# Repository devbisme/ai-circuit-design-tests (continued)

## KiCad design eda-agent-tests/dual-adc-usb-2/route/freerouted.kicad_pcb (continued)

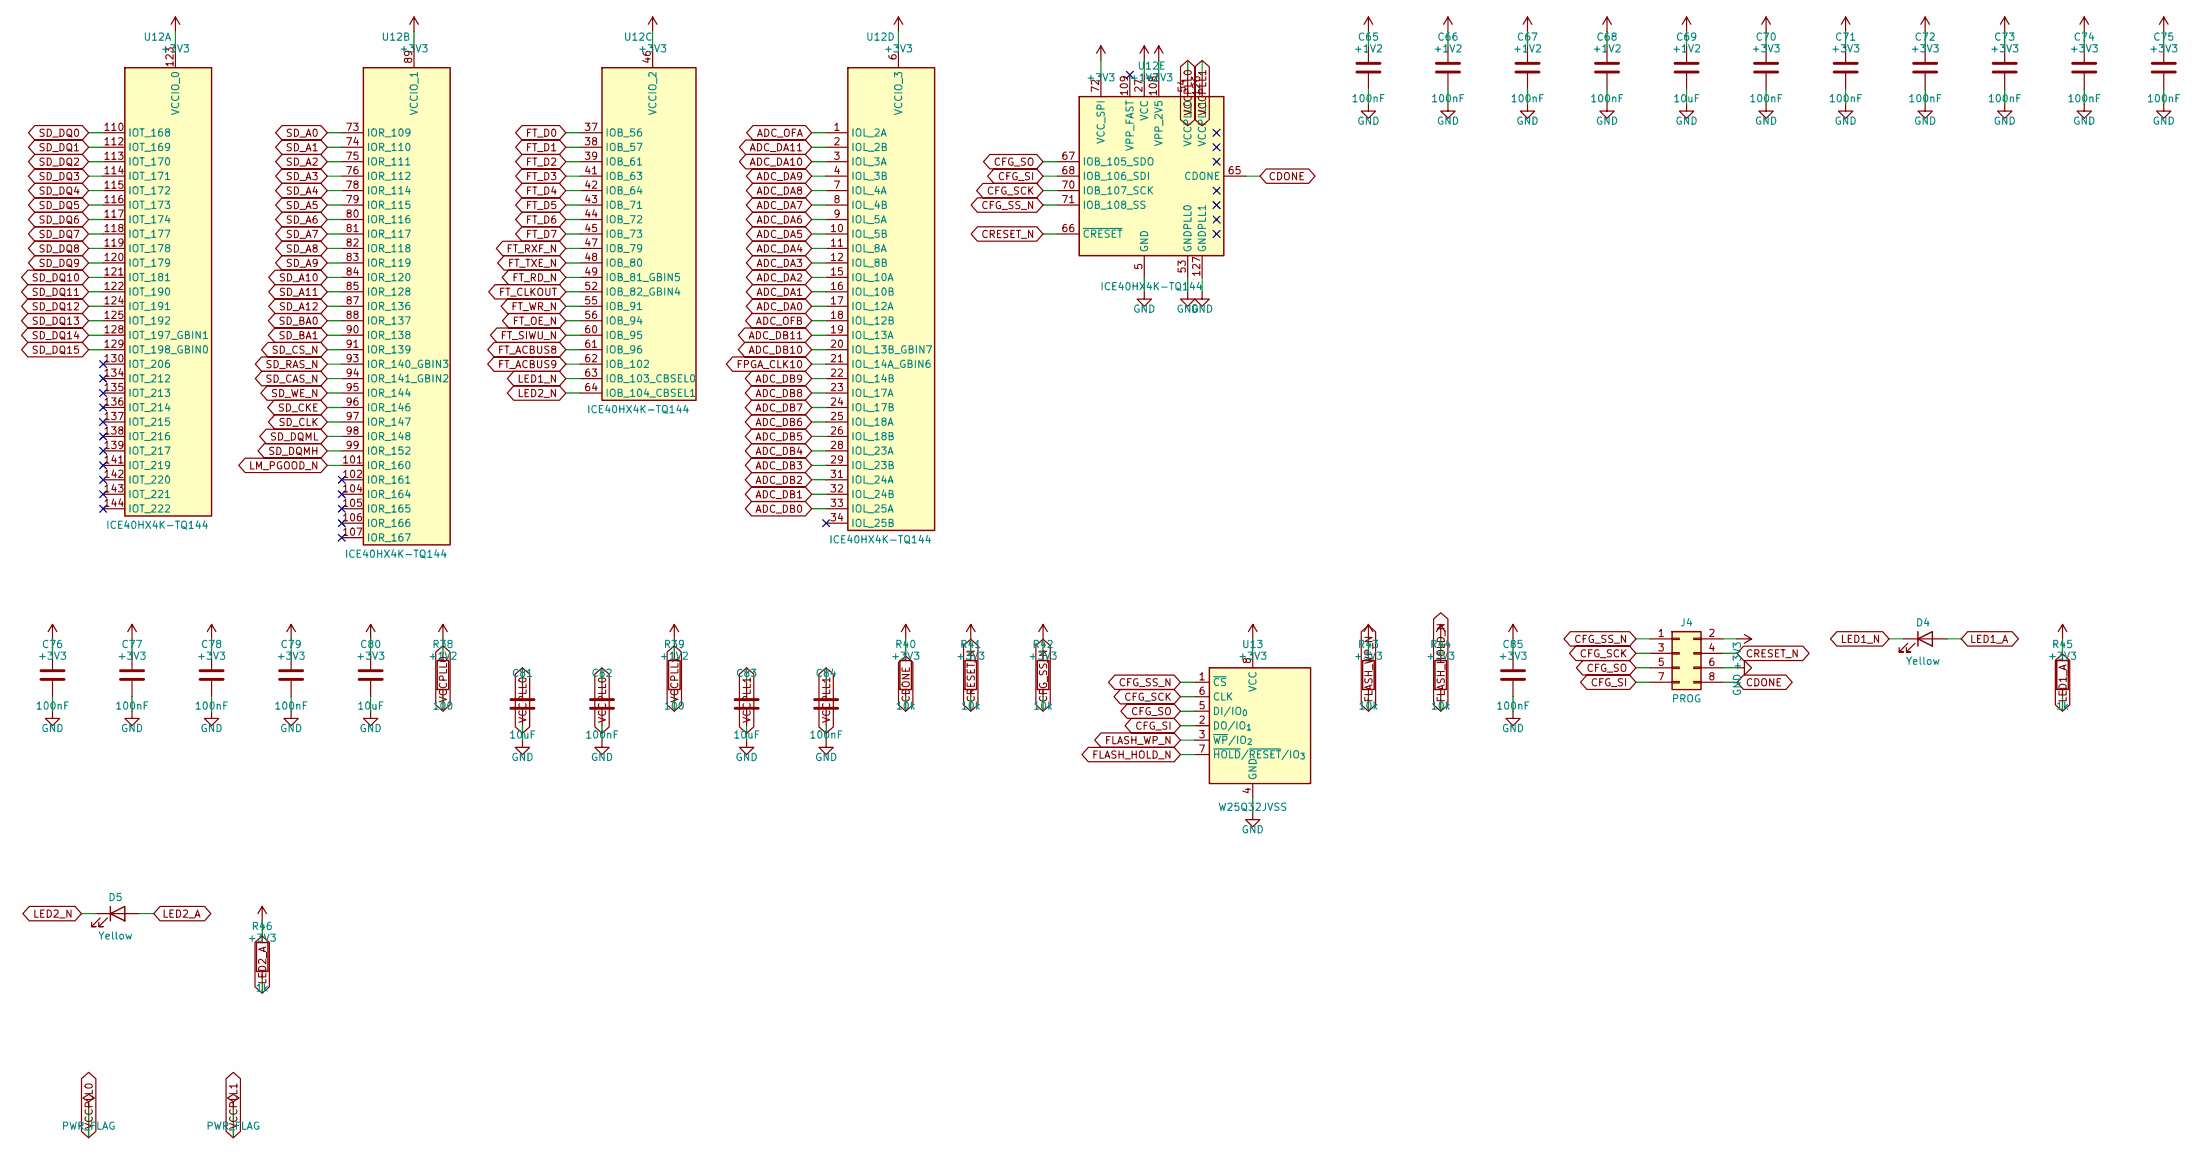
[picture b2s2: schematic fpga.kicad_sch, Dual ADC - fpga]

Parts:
C65, C66, C67, C68, C70, C71, C72, C73, C74, C75, C76, C77, C78, C79, C82, C84, C85: 100nF; C_0603_1608Metric
C69, C80, C81, C83: 10uF; C_0805_2012Metric
D4, D5: Yellow; LED_0603_1608Metric
J4: PROG; PinHeader_2x04_P2.54mm_Vertical
R38, R39: 100; R_0603_1608Metric
R40, R41, R42, R43, R44: 10k; R_0603_1608Metric
R45, R46: 1k; R_0603_1608Metric
U12: ICE40HX4K-TQ144; TQFP-144_20x20mm_P0.5mm; MPN ICE40HX4K-TQ144
U13: W25Q32JVSS; SOIC-8_5.3x5.3mm_P1.27mm; MPN W25Q32JVSSIQ

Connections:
+1V2: C65.1, C66.1, C67.1, C68.1, C69.1, R38.1, R39.1, U12.27 (VCC), U12.40 (VCC), U12.92 (VCC), U12.111 (VCC); also elsewhere on the board
ADC_DA0: U12.17 (IOL_12A); also elsewhere on the board
ADC_DA1: U12.16 (IOL_10B); also elsewhere on the board
ADC_DA2: U12.15 (IOL_10A); also elsewhere on the board
ADC_DA3: U12.12 (IOL_8B); also elsewhere on the board
ADC_DA4: U12.11 (IOL_8A); also elsewhere on the board
ADC_DA5: U12.10 (IOL_5B); also elsewhere on the board
ADC_DA6: U12.9 (IOL_5A); also elsewhere on the board
ADC_DA7: U12.8 (IOL_4B); also elsewhere on the board
ADC_DA8: U12.7 (IOL_4A); also elsewhere on the board
ADC_DA9: U12.4 (IOL_3B); also elsewhere on the board
ADC_DA10: U12.3 (IOL_3A); also elsewhere on the board
ADC_DA11: U12.2 (IOL_2B); also elsewhere on the board
ADC_DB0: U12.33 (IOL_25A); also elsewhere on the board
ADC_DB1: U12.32 (IOL_24B); also elsewhere on the board
ADC_DB2: U12.31 (IOL_24A); also elsewhere on the board
ADC_DB3: U12.29 (IOL_23B); also elsewhere on the board
ADC_DB4: U12.28 (IOL_23A); also elsewhere on the board
ADC_DB5: U12.26 (IOL_18B); also elsewhere on the board
ADC_DB6: U12.25 (IOL_18A); also elsewhere on the board
ADC_DB7: U12.24 (IOL_17B); also elsewhere on the board
ADC_DB8: U12.23 (IOL_17A); also elsewhere on the board
ADC_DB9: U12.22 (IOL_14B); also elsewhere on the board
ADC_DB10: U12.20 (IOL_13B_GBIN7); also elsewhere on the board
ADC_DB11: U12.19 (IOL_13A); also elsewhere on the board
ADC_OFA: U12.1 (IOL_2A); also elsewhere on the board
ADC_OFB: U12.18 (IOL_12B); also elsewhere on the board
CDONE: J4.8, R40.2, U12.65 (CDONE)
CFG_SCK: J4.3, U12.70 (IOB_107_SCK), U13.6 (CLK)
CFG_SI: J4.7, U12.68 (IOB_106_SDI), U13.2 (DO/IO_{1})
CFG_SO: J4.5, U12.67 (IOB_105_SDO), U13.5 (DI/IO_{0})
CFG_SS_N: J4.1, R42.2, U12.71 (IOB_108_SS), U13.1 (~CS)
CRESET_N: J4.4, R41.2, U12.66 (~CRESET)
FLASH_HOLD_N: R44.2, U13.7 (~HOLD/~RESET/IO_{3})
FLASH_WP_N: R43.2, U13.3 (~WP/IO_{2})
FPGA_CLK10: U12.21 (IOL_14A_GBIN6); also elsewhere on the board
FT_ACBUS8: U12.61 (IOB_96); also elsewhere on the board
FT_ACBUS9: U12.62 (IOB_102); also elsewhere on the board
FT_CLKOUT: U12.52 (IOB_82_GBIN4); also elsewhere on the board
FT_D0: U12.37 (IOB_56); also elsewhere on the board
FT_D1: U12.38 (IOB_57); also elsewhere on the board
FT_D2: U12.39 (IOB_61); also elsewhere on the board
FT_D3: U12.41 (IOB_63); also elsewhere on the board
FT_D4: U12.42 (IOB_64); also elsewhere on the board
FT_D5: U12.43 (IOB_71); also elsewhere on the board
FT_D6: U12.44 (IOB_72); also elsewhere on the board
FT_D7: U12.45 (IOB_73); also elsewhere on the board
FT_OE_N: U12.56 (IOB_94); also elsewhere on the board
FT_RD_N: U12.49 (IOB_81_GBIN5); also elsewhere on the board
FT_RXF_N: U12.47 (IOB_79); also elsewhere on the board
FT_SIWU_N: U12.60 (IOB_95); also elsewhere on the board
FT_TXE_N: U12.48 (IOB_80); also elsewhere on the board
FT_WR_N: U12.55 (IOB_91); also elsewhere on the board
LED1_A: D4.2 (A), R45.2
LED1_N: D4.1 (K), U12.63 (IOB_103_CBSEL0)
LED2_A: D5.2 (A), R46.2
LED2_N: D5.1 (K), U12.64 (IOB_104_CBSEL1)
LM_PGOOD_N: U12.101 (IOR_160); also elsewhere on the board
SD_A0: U12.73 (IOR_109); also elsewhere on the board
SD_A1: U12.74 (IOR_110); also elsewhere on the board
SD_A2: U12.75 (IOR_111); also elsewhere on the board
SD_A3: U12.76 (IOR_112); also elsewhere on the board
SD_A4: U12.78 (IOR_114); also elsewhere on the board
SD_A5: U12.79 (IOR_115); also elsewhere on the board
SD_A6: U12.80 (IOR_116); also elsewhere on the board
SD_A7: U12.81 (IOR_117); also elsewhere on the board
SD_A8: U12.82 (IOR_118); also elsewhere on the board
SD_A9: U12.83 (IOR_119); also elsewhere on the board
SD_A10: U12.84 (IOR_120); also elsewhere on the board
SD_A11: U12.85 (IOR_128); also elsewhere on the board
SD_A12: U12.87 (IOR_136); also elsewhere on the board
SD_BA0: U12.88 (IOR_137); also elsewhere on the board
SD_BA1: U12.90 (IOR_138); also elsewhere on the board
SD_CAS_N: U12.94 (IOR_141_GBIN2); also elsewhere on the board
SD_CKE: U12.96 (IOR_146); also elsewhere on the board
SD_CLK: U12.97 (IOR_147); also elsewhere on the board
SD_CS_N: U12.91 (IOR_139); also elsewhere on the board
SD_DQ0: U12.110 (IOT_168); also elsewhere on the board
SD_DQ1: U12.112 (IOT_169); also elsewhere on the board
SD_DQ2: U12.113 (IOT_170); also elsewhere on the board
SD_DQ3: U12.114 (IOT_171); also elsewhere on the board
SD_DQ4: U12.115 (IOT_172); also elsewhere on the board
SD_DQ5: U12.116 (IOT_173); also elsewhere on the board
SD_DQ6: U12.117 (IOT_174); also elsewhere on the board
SD_DQ7: U12.118 (IOT_177); also elsewhere on the board
SD_DQ8: U12.119 (IOT_178); also elsewhere on the board
SD_DQ9: U12.120 (IOT_179); also elsewhere on the board
SD_DQ10: U12.121 (IOT_181); also elsewhere on the board
SD_DQ11: U12.122 (IOT_190); also elsewhere on the board
SD_DQ12: U12.124 (IOT_191); also elsewhere on the board
SD_DQ13: U12.125 (IOT_192); also elsewhere on the board
SD_DQ14: U12.128 (IOT_197_GBIN1); also elsewhere on the board
SD_DQ15: U12.129 (IOT_198_GBIN0); also elsewhere on the board
SD_DQMH: U12.99 (IOR_152); also elsewhere on the board
SD_DQML: U12.98 (IOR_148); also elsewhere on the board
SD_RAS_N: U12.93 (IOR_140_GBIN3); also elsewhere on the board
SD_WE_N: U12.95 (IOR_144); also elsewhere on the board
VCCPLL0: C81.1, C82.1, R38.2, U12.54 (VCCPLL0)
VCCPLL1: C83.1, C84.1, R39.2, U12.126 (VCCPLL1)

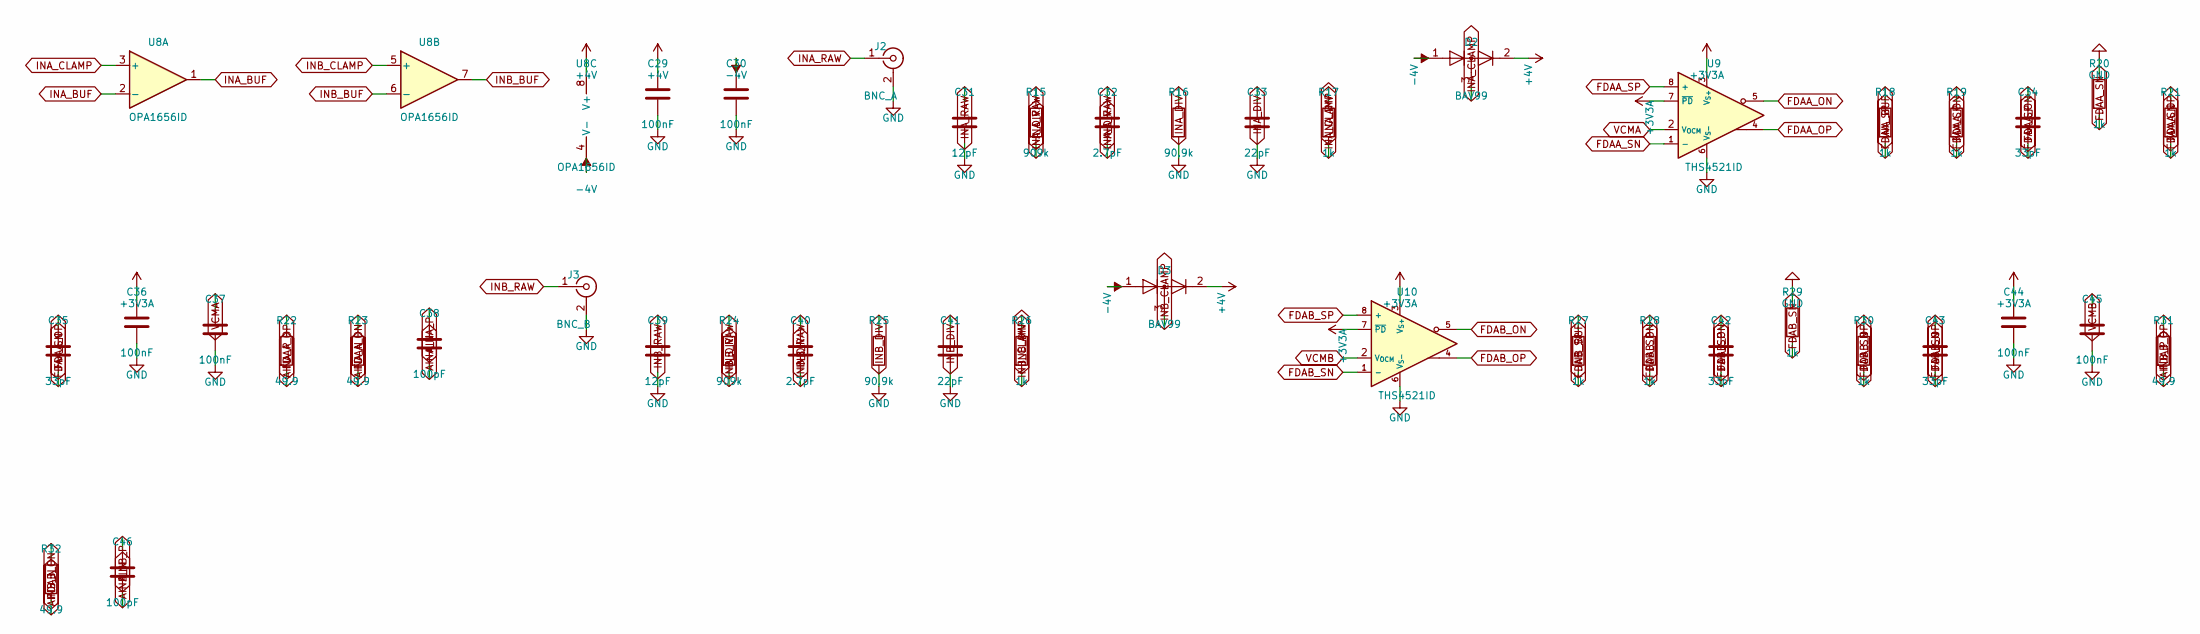
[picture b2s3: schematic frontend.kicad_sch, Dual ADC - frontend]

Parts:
C29, C30, C36, C37, C44, C45: 100nF; C_0603_1608Metric
C31, C39: 12pF; C_0603_1608Metric
C32, C40: 2.7pF; C_0603_1608Metric
C33, C41: 22pF; C_0603_1608Metric
C34, C35, C42, C43: 33pF; C_0603_1608Metric
C38, C46: 100pF; C_0603_1608Metric
D2, D3: BAV99; SOT-23; MPN BAV99,215
J2: BNC_A; BNC_Amphenol_B6252HB-NPP3G-50_Horizontal; MPN B6252HB-NPP3G-50
J3: BNC_B; BNC_Amphenol_B6252HB-NPP3G-50_Horizontal; MPN B6252HB-NPP3G-50
R15, R24: 909k; R_0603_1608Metric; Tolerance 0.1%
R16, R25: 90.9k; R_0603_1608Metric; Tolerance 0.1%
R17, R18, R19, R20, R21, R26, R27, R28, R29, R30: 1k; R_0603_1608Metric
R22, R23, R31, R32: 49.9; R_0603_1608Metric
U8: OPA1656ID; SOIC-8_3.9x4.9mm_P1.27mm; MPN OPA1656IDR
U9, U10: THS4521ID; SOIC-8_3.9x4.9mm_P1.27mm; MPN THS4521IDR

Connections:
+3V3A: C36.1, C44.1, U9.3 (V_{S+}), U9.7 (~PD), U10.3 (V_{S+}), U10.7 (~PD); also elsewhere on the board
+4V: C29.1, D2.2 (A), D3.2 (A), U8.8 (V+); also elsewhere on the board
-4V: C30.1, D2.1 (K), D3.1 (K), U8.4 (V-); also elsewhere on the board
AINA_N: C38.2, R23.2; also elsewhere on the board
AINA_P: C38.1, R22.2; also elsewhere on the board
AINB_N: C46.2, R32.2; also elsewhere on the board
AINB_P: C46.1, R31.2; also elsewhere on the board
FDAA_ON: C34.1, R19.1, R23.1, U9.5
FDAA_OP: C35.1, R21.1, R22.1, U9.4
FDAA_SN: C35.2, R20.2, R21.2, U9.1 (-)
FDAA_SP: C34.2, R18.2, R19.2, U9.8 (+)
FDAB_ON: C42.1, R28.1, R32.1, U10.5
FDAB_OP: C43.1, R30.1, R31.1, U10.4
FDAB_SN: C43.2, R29.2, R30.2, U10.1 (-)
FDAB_SP: C42.2, R27.2, R28.2, U10.8 (+)
INA_BUF: R18.1, U8.1, U8.2 (-)
INA_CLAMP: D2.3 (K), R17.2, U8.3 (+)
INA_DIV: C32.2, C33.1, R15.2, R16.1, R17.1
INA_RAW: C31.1, C32.1, J2.1 (In), R15.1
INB_BUF: R27.1, U8.6 (-), U8.7
INB_CLAMP: D3.3 (K), R26.2, U8.5 (+)
INB_DIV: C40.2, C41.1, R24.2, R25.1, R26.1
INB_RAW: C39.1, C40.1, J3.1 (In), R24.1
VCMA: C37.1, U9.2 (V_{OCM}); also elsewhere on the board
VCMB: C45.1, U10.2 (V_{OCM}); also elsewhere on the board

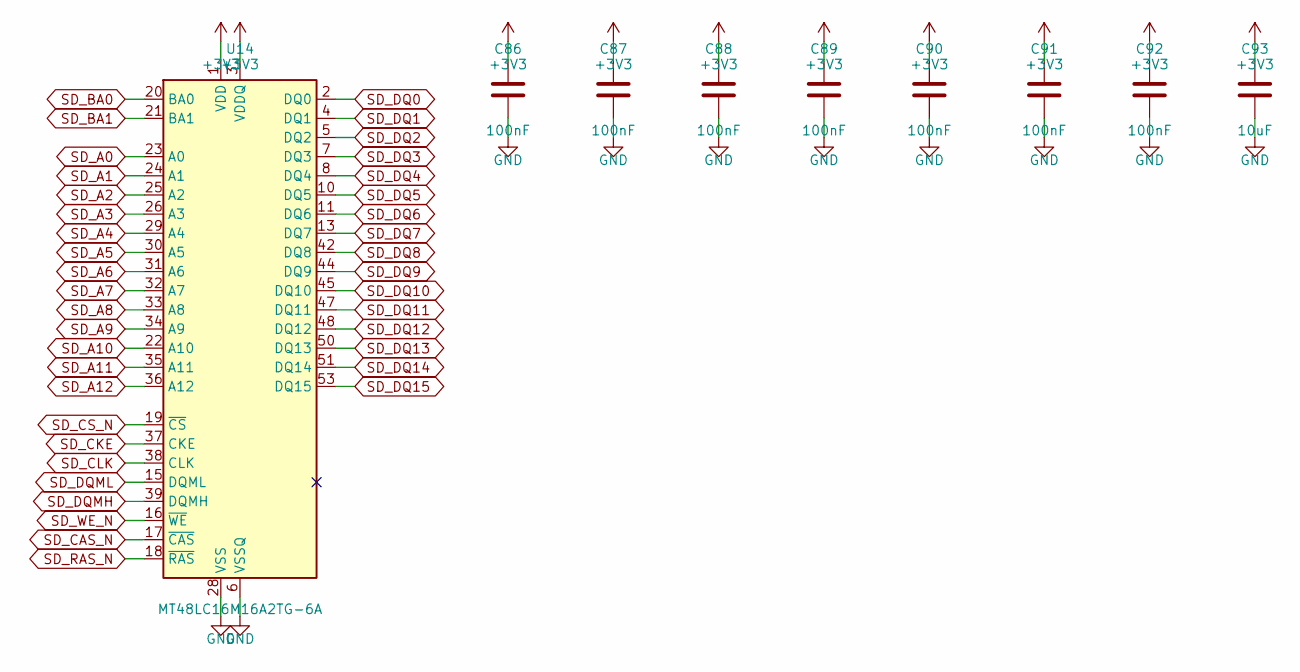
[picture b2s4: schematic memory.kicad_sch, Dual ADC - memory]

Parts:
C86, C87, C88, C89, C90, C91, C92: 100nF; C_0603_1608Metric
C93: 10uF; C_0805_2012Metric
U14: MT48LC16M16A2TG-6A; TSOP-II-54_22.2x10.16mm_P0.8mm; MPN MT48LC16M16A2P-6A:G

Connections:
SD_A0: U14.23 (A0); also elsewhere on the board
SD_A1: U14.24 (A1); also elsewhere on the board
SD_A2: U14.25 (A2); also elsewhere on the board
SD_A3: U14.26 (A3); also elsewhere on the board
SD_A4: U14.29 (A4); also elsewhere on the board
SD_A5: U14.30 (A5); also elsewhere on the board
SD_A6: U14.31 (A6); also elsewhere on the board
SD_A7: U14.32 (A7); also elsewhere on the board
SD_A8: U14.33 (A8); also elsewhere on the board
SD_A9: U14.34 (A9); also elsewhere on the board
SD_A10: U14.22 (A10); also elsewhere on the board
SD_A11: U14.35 (A11); also elsewhere on the board
SD_A12: U14.36 (A12); also elsewhere on the board
SD_BA0: U14.20 (BA0); also elsewhere on the board
SD_BA1: U14.21 (BA1); also elsewhere on the board
SD_CAS_N: U14.17 (~CAS); also elsewhere on the board
SD_CKE: U14.37 (CKE); also elsewhere on the board
SD_CLK: U14.38 (CLK); also elsewhere on the board
SD_CS_N: U14.19 (~CS); also elsewhere on the board
SD_DQ0: U14.2 (DQ0); also elsewhere on the board
SD_DQ1: U14.4 (DQ1); also elsewhere on the board
SD_DQ2: U14.5 (DQ2); also elsewhere on the board
SD_DQ3: U14.7 (DQ3); also elsewhere on the board
SD_DQ4: U14.8 (DQ4); also elsewhere on the board
SD_DQ5: U14.10 (DQ5); also elsewhere on the board
SD_DQ6: U14.11 (DQ6); also elsewhere on the board
SD_DQ7: U14.13 (DQ7); also elsewhere on the board
SD_DQ8: U14.42 (DQ8); also elsewhere on the board
SD_DQ9: U14.44 (DQ9); also elsewhere on the board
SD_DQ10: U14.45 (DQ10); also elsewhere on the board
SD_DQ11: U14.47 (DQ11); also elsewhere on the board
SD_DQ12: U14.48 (DQ12); also elsewhere on the board
SD_DQ13: U14.50 (DQ13); also elsewhere on the board
SD_DQ14: U14.51 (DQ14); also elsewhere on the board
SD_DQ15: U14.53 (DQ15); also elsewhere on the board
SD_DQMH: U14.39 (DQMH); also elsewhere on the board
SD_DQML: U14.15 (DQML); also elsewhere on the board
SD_RAS_N: U14.18 (~RAS); also elsewhere on the board
SD_WE_N: U14.16 (~WE); also elsewhere on the board

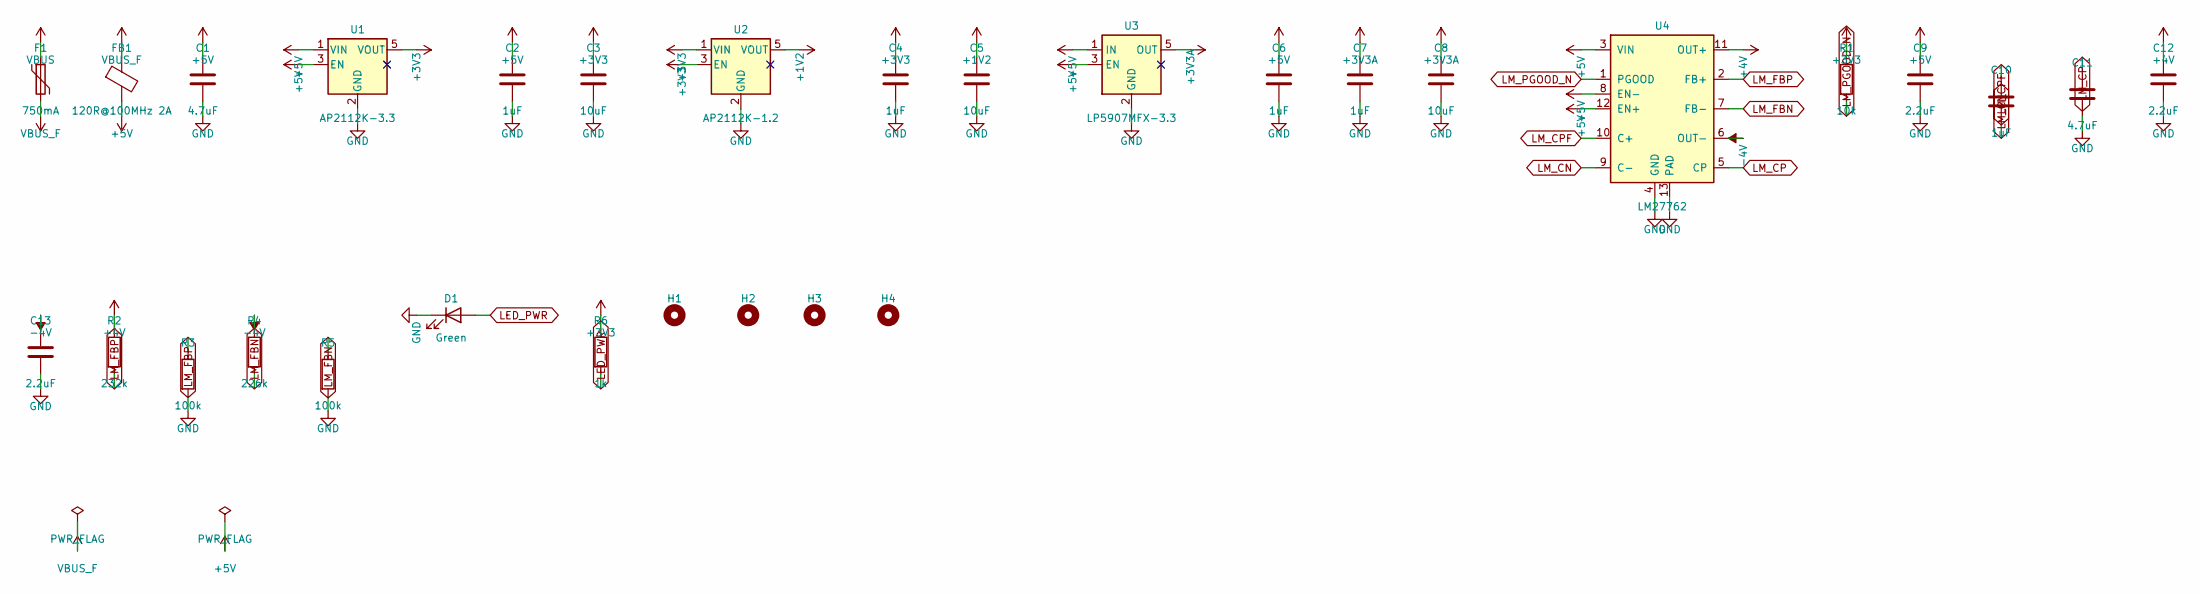
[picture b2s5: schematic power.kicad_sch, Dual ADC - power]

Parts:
C1, C11: 4.7uF; C_0805_2012Metric
C2, C4, C6, C7: 1uF; C_0603_1608Metric
C3, C5, C8: 10uF; C_0805_2012Metric
C9, C12, C13: 2.2uF; C_0805_2012Metric
C10: 1uF; C_0402_1005Metric
D1: Green; LED_0603_1608Metric
F1: 750mA; Fuse_1206_3216Metric; MPN 0ZCJ0050AF2E
FB1: 120R@100MHz 2A; L_0603_1608Metric; MPN BLM18AG601SN1D
H1, H2, H3, H4: MountingHole; MountingHole_3.2mm_M3
R1: 10k; R_0603_1608Metric
R2: 232k; R_0603_1608Metric
R3, R5: 100k; R_0603_1608Metric
R4: 226k; R_0603_1608Metric
R6: 1k; R_0603_1608Metric
U1: AP2112K-3.3; SOT-23-5; MPN AP2112K-3.3TRG1
U2: AP2112K-1.2; SOT-23-5; MPN AP2112K-1.2TRG1
U3: LP5907MFX-3.3; SOT-23-5; MPN LP5907MFX-3.3/NOPB
U4: LM27762; WSON-12-1EP_3x2mm_P0.5mm_EP1x2.65; MPN LM27762DSSR

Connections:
+1V2: C5.1, U2.5 (VOUT); also elsewhere on the board
+3V3A: C7.1, C8.1, U3.5 (OUT); also elsewhere on the board
+4V: C12.1, R2.1, U4.11 (OUT+); also elsewhere on the board
+5V: C1.1, C2.1, C6.1, C9.1, FB1.2, U1.1 (VIN), U1.3 (EN), U3.1 (IN), U3.3 (EN), U4.3 (VIN), U4.8 (EN-), U4.12 (EN+)
-4V: C13.1, R4.1, U4.6 (OUT-); also elsewhere on the board
LED_PWR: D1.2 (A), R6.2
LM_CN: C10.2, U4.9 (C-)
LM_CP: C11.1, U4.5 (CP)
LM_CPF: C10.1, U4.10 (C+)
LM_FBN: R4.2, R5.1, U4.7 (FB-)
LM_FBP: R2.2, R3.1, U4.2 (FB+)
LM_PGOOD_N: R1.2, U4.1 (PGOOD); also elsewhere on the board
VBUS: F1.1; also elsewhere on the board
VBUS_F: F1.2, FB1.1; also elsewhere on the board

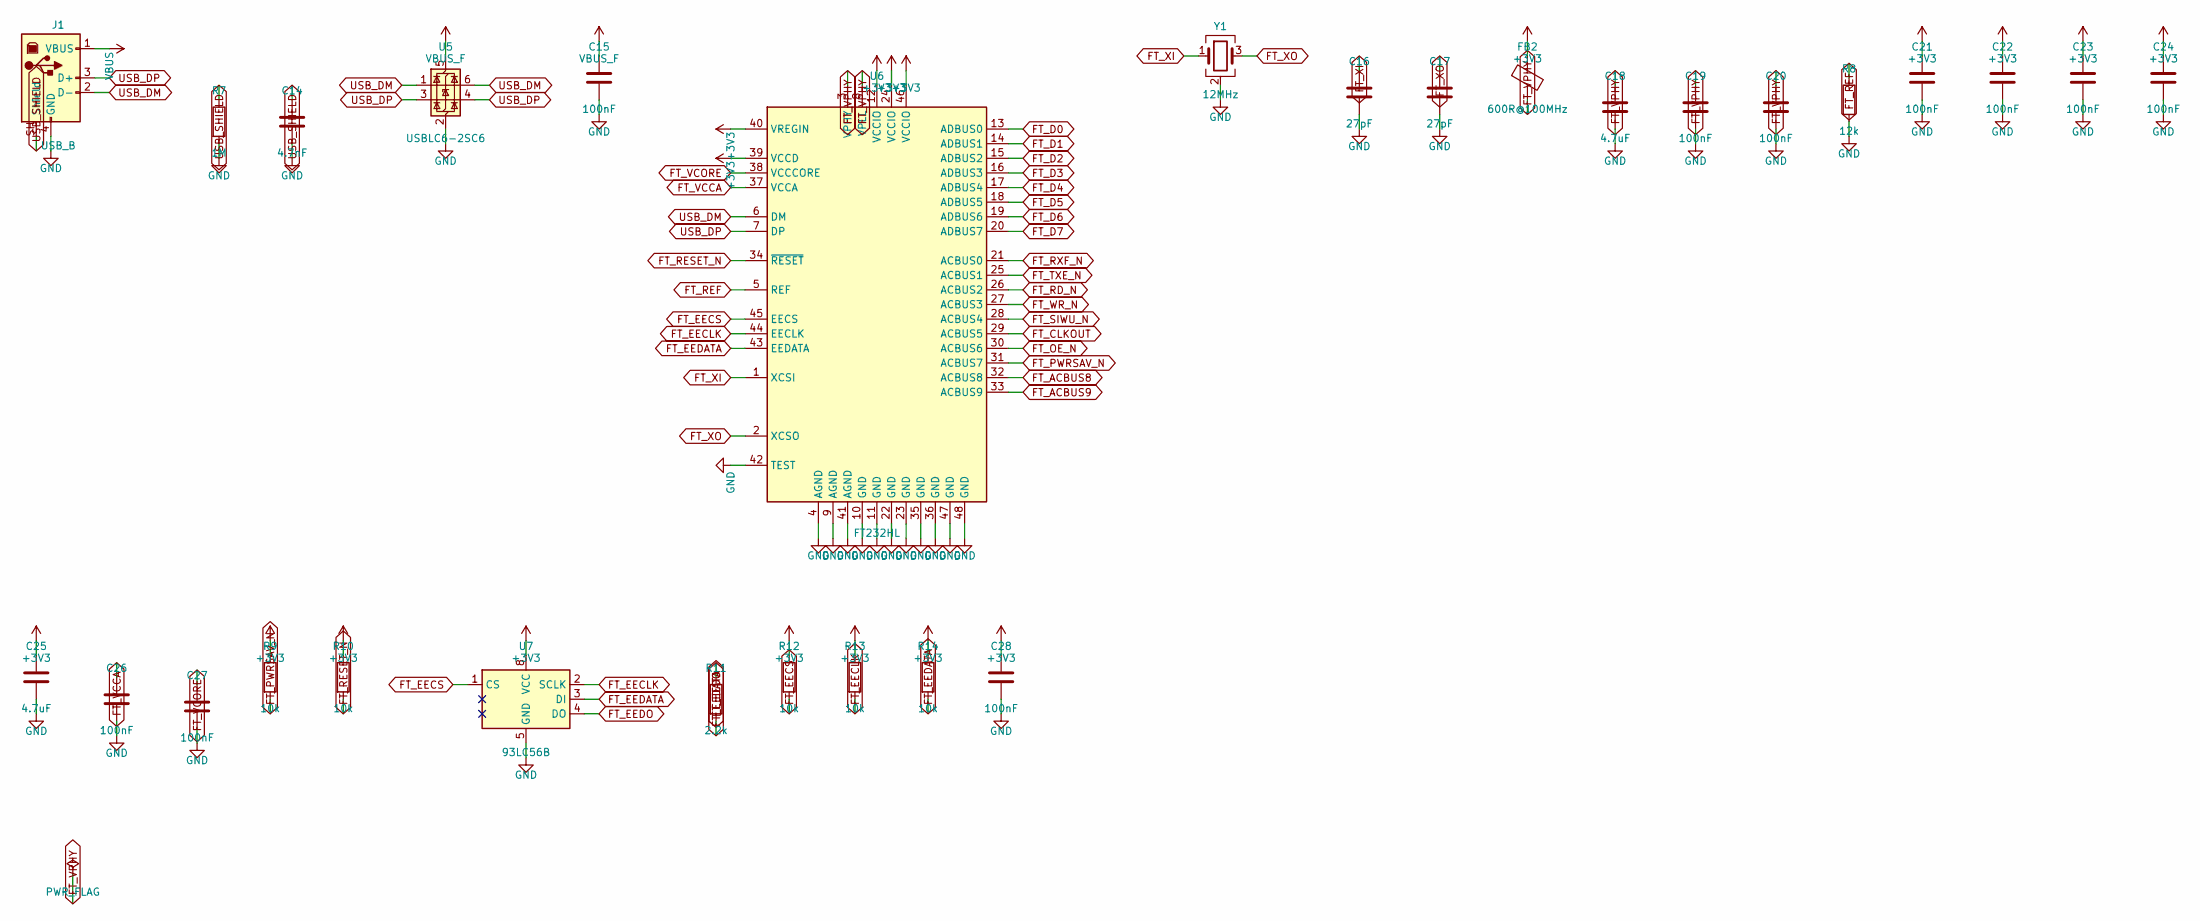
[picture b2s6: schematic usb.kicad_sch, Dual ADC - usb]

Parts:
C14: 4.7nF; C_0603_1608Metric
C15, C19, C20, C21, C22, C23, C24, C26, C27, C28: 100nF; C_0603_1608Metric
C16, C17: 27pF; C_0603_1608Metric
C18, C25: 4.7uF; C_0805_2012Metric
FB2: 600R@100MHz; L_0603_1608Metric; MPN BLM18AG601SN1D
J1: USB_B; USB_B_OST_USB-B1HSxx_Horizontal; MPN USB-B1HSW6
R7: 1M; R_0603_1608Metric
R8: 12k; R_0603_1608Metric; Tolerance 1%
R9, R10, R12, R13, R14: 10k; R_0603_1608Metric
R11: 2.2k; R_0603_1608Metric
U5: USBLC6-2SC6; SOT-23-6; MPN USBLC6-2SC6
U6: FT232HL; LQFP-48_7x7mm_P0.5mm; MPN FT232HL-REEL
U7: 93LC56B; SOIC-8_3.9x4.9mm_P1.27mm; MPN 93LC56BT-I/SN
Y1: 12MHz; Crystal_SMD_3225-4Pin_3.2x2.5mm; MPN ABM8-12.000MHZ-B2-T

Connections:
FT_ACBUS8: U6.32 (ACBUS8); also elsewhere on the board
FT_ACBUS9: U6.33 (ACBUS9); also elsewhere on the board
FT_CLKOUT: U6.29 (ACBUS5); also elsewhere on the board
FT_D0: U6.13 (ADBUS0); also elsewhere on the board
FT_D1: U6.14 (ADBUS1); also elsewhere on the board
FT_D2: U6.15 (ADBUS2); also elsewhere on the board
FT_D3: U6.16 (ADBUS3); also elsewhere on the board
FT_D4: U6.17 (ADBUS4); also elsewhere on the board
FT_D5: U6.18 (ADBUS5); also elsewhere on the board
FT_D6: U6.19 (ADBUS6); also elsewhere on the board
FT_D7: U6.20 (ADBUS7); also elsewhere on the board
FT_EECLK: R13.2, U6.44 (EECLK), U7.2 (SCLK)
FT_EECS: R12.2, U6.45 (EECS), U7.1 (CS)
FT_EEDATA: R11.2, R14.2, U6.43 (EEDATA), U7.3 (DI)
FT_EEDO: R11.1, U7.4 (DO)
FT_OE_N: U6.30 (ACBUS6); also elsewhere on the board
FT_PWRSAV_N: R9.2, U6.31 (ACBUS7)
FT_RD_N: U6.26 (ACBUS2); also elsewhere on the board
FT_REF: R8.1, U6.5 (REF)
FT_RESET_N: R10.2, U6.34 (~RESET)
FT_RXF_N: U6.21 (ACBUS0); also elsewhere on the board
FT_SIWU_N: U6.28 (ACBUS4); also elsewhere on the board
FT_TXE_N: U6.25 (ACBUS1); also elsewhere on the board
FT_VCCA: C26.1, U6.37 (VCCA)
FT_VCORE: C27.1, U6.38 (VCCCORE)
FT_VPHY: C18.1, C19.1, C20.1, FB2.2, U6.3 (VPHY), U6.8 (VPLL)
FT_WR_N: U6.27 (ACBUS3); also elsewhere on the board
FT_XI: C16.1, U6.1 (XCSI), Y1.1
FT_XO: C17.1, U6.2 (XCSO), Y1.3
USB_DM: J1.2 (D-), U5.1 (I/O1), U5.6 (I/O1), U6.6 (DM)
USB_DP: J1.3 (D+), U5.3 (I/O2), U5.4 (I/O2), U6.7 (DP)
USB_SHIELD: C14.1, J1.SH (Shield), R7.1
VBUS: J1.1 (VBUS); also elsewhere on the board
VBUS_F: C15.1, U5.5 (VBUS); also elsewhere on the board

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
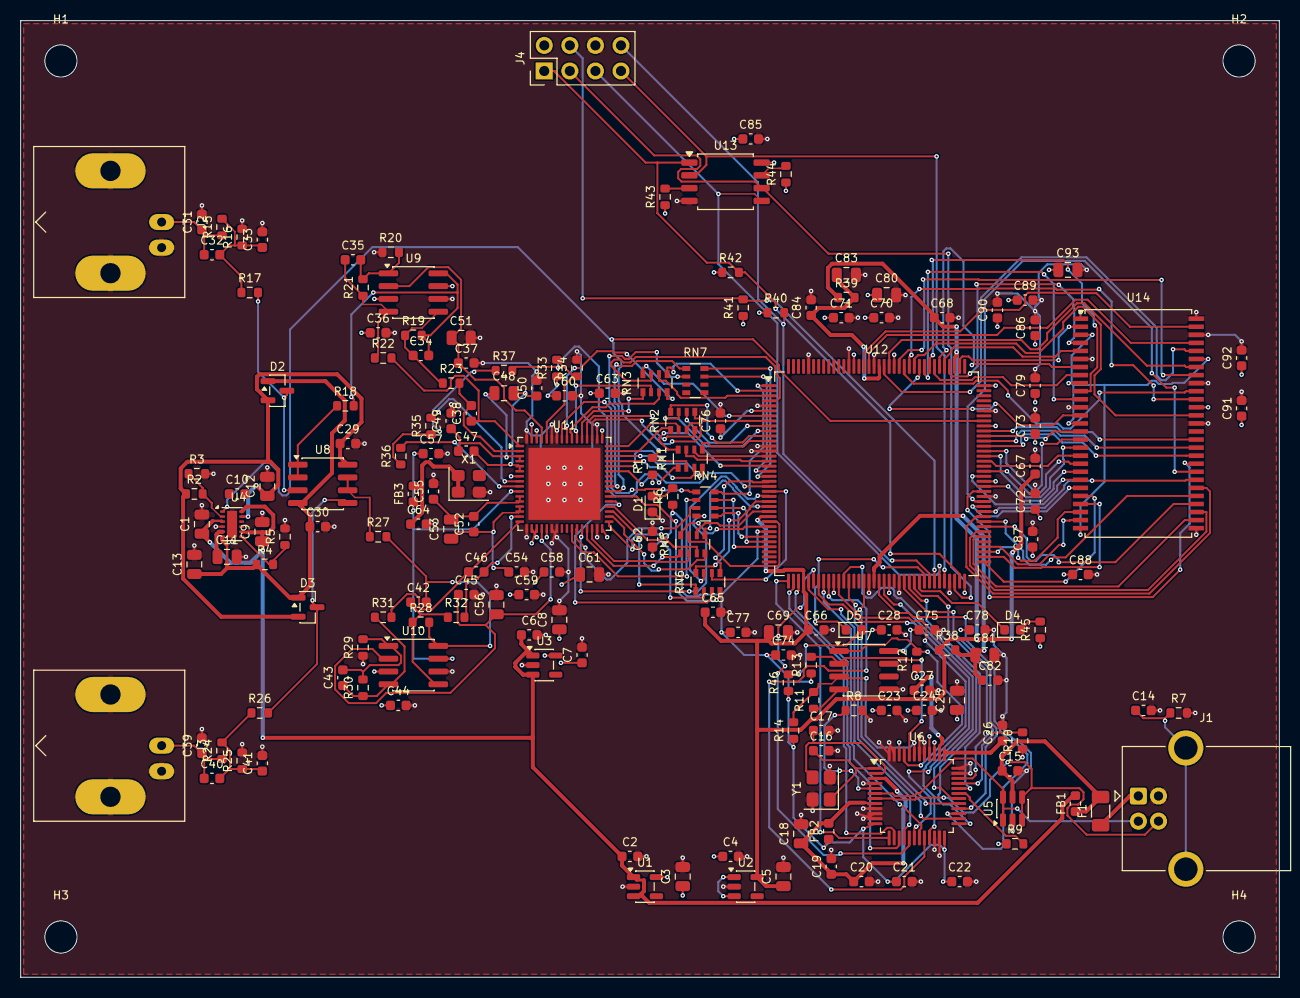
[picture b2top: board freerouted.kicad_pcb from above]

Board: 4 copper layers, 125.0 x 95.0 mm, 179 parts (0 on the bottom side), 185 nets.

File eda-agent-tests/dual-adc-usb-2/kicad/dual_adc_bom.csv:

"Refs","Value","Footprint","MPN","Manufacturer","Tolerance","Qty"
"C1,C11,C18,C25","4.7uF","Capacitor_SMD:C_0805_2012Metric","","","","4"
"C2,C4,C6,C7,C49,C50,C54,C55","1uF","Capacitor_SMD:C_0603_1608Metric","","","","8"
"C3,C5,C8,C61,C69,C80,C81,C83,C93","10uF","Capacitor_SMD:C_0805_2012Metric","","","","9"
"C9,C12,C13,C48,C51,C53,C56","2.2uF","Capacitor_SMD:C_0805_2012Metric","","","","7"
"C10","1uF","Capacitor_SMD:C_0402_1005Metric","","","","1"
"C14","4.7nF","Capacitor_SMD:C_0603_1608Metric","","","","1"
"C15,C19-C24,C26-C30,C36,C37,C44,C45,C47,C52,C57-C60,C62-C68,C70-C79,C82,C84-C92","100nF","Capacitor_SMD:C_0603_1608Metric","","","","49"
"C16,C17","27pF","Capacitor_SMD:C_0603_1608Metric","","","","2"
"C31,C39","12pF","Capacitor_SMD:C_0603_1608Metric","","","","2"
"C32,C40","2.7pF","Capacitor_SMD:C_0603_1608Metric","","","","2"
"C33,C41","22pF","Capacitor_SMD:C_0603_1608Metric","","","","2"
"C34,C35,C42,C43","33pF","Capacitor_SMD:C_0603_1608Metric","","","","4"
"C38,C46","100pF","Capacitor_SMD:C_0603_1608Metric","","","","2"
"D1","Green","LED_SMD:LED_0603_1608Metric","","","","1"
"D2,D3","BAV99","Package_TO_SOT_SMD:SOT-23","BAV99,215","Nexperia","","2"
"D4,D5","Yellow","LED_SMD:LED_0603_1608Metric","","","","2"
"F1","750mA","Fuse:Fuse_1206_3216Metric","0ZCJ0050AF2E","Bel Fuse","","1"
"FB1","120R@100MHz 2A","Inductor_SMD:L_0603_1608Metric","BLM18AG601SN1D","Murata","","1"
"FB2,FB3","600R@100MHz","Inductor_SMD:L_0603_1608Metric","BLM18AG601SN1D","Murata","","2"
"J1","USB_B","Connector_USB:USB_B_OST_USB-B1HSxx_Horizontal","USB-B1HSW6","On Shore Technology","","1"
"J2","BNC_A","Connector_Coaxial:BNC_Amphenol_B6252HB-NPP3G-50_Horizontal","B6252HB-NPP3G-50","Amphenol RF","","1"
"J3","BNC_B","Connector_Coaxial:BNC_Amphenol_B6252HB-NPP3G-50_Horizontal","B6252HB-NPP3G-50","Amphenol RF","","1"
"J4","PROG","Connector_PinHeader_2.54mm:PinHeader_2x04_P2.54mm_Vertical","","","","1"
"R1,R9,R10,R12-R14,R33,R40-R44","10k","Resistor_SMD:R_0603_1608Metric","","","","12"
"R2","232k","Resistor_SMD:R_0603_1608Metric","","","","1"
"R3,R5","100k","Resistor_SMD:R_0603_1608Metric","","","","2"
"R4","226k","Resistor_SMD:R_0603_1608Metric","","","","1"
"R6,R17-R21,R26-R30,R45,R46","1k","Resistor_SMD:R_0603_1608Metric","","","","13"
"R7","1M","Resistor_SMD:R_0603_1608Metric","","","","1"
"R8","12k","Resistor_SMD:R_0603_1608Metric","","","1%","1"
"R11","2.2k","Resistor_SMD:R_0603_1608Metric","","","","1"
"R15,R24","909k","Resistor_SMD:R_0603_1608Metric","","","0.1%","2"
"R16,R25","90.9k","Resistor_SMD:R_0603_1608Metric","","","0.1%","2"
"R22,R23,R31,R32","49.9","Resistor_SMD:R_0603_1608Metric","","","","4"
"R34","20k","Resistor_SMD:R_0603_1608Metric","","","","1"
"R35-R37","33","Resistor_SMD:R_0603_1608Metric","","","","3"
"R38,R39","100","Resistor_SMD:R_0603_1608Metric","","","","2"
"RN1-RN7","33","Resistor_SMD:R_Array_Convex_4x0603","CAY16-330J4LF","Bourns","","7"
"U1","AP2112K-3.3","Package_TO_SOT_SMD:SOT-23-5","AP2112K-3.3TRG1","Diodes Inc","","1"
"U2","AP2112K-1.2","Package_TO_SOT_SMD:SOT-23-5","AP2112K-1.2TRG1","Diodes Inc","","1"
"U3","LP5907MFX-3.3","Package_TO_SOT_SMD:SOT-23-5","LP5907MFX-3.3/NOPB","Texas Instruments","","1"
"U4","LM27762","Package_SON:WSON-12-1EP_3x2mm_P0.5mm_EP1x2.65","LM27762DSSR","Texas Instruments","","1"
"U5","USBLC6-2SC6","Package_TO_SOT_SMD:SOT-23-6","USBLC6-2SC6","STMicroelectronics","","1"
"U6","FT232HL","Package_QFP:LQFP-48_7x7mm_P0.5mm","FT232HL-REEL","FTDI","","1"
"U7","93LC56B","Package_SO:SOIC-8_3.9x4.9mm_P1.27mm","93LC56BT-I/SN","Microchip","","1"
"U8","OPA1656ID","Package_SO:SOIC-8_3.9x4.9mm_P1.27mm","OPA1656IDR","Texas Instruments","","1"
"U9,U10","THS4521ID","Package_SO:SOIC-8_3.9x4.9mm_P1.27mm","THS4521IDR","Texas Instruments","","2"
"U11","LTC2290CUP","Package_DFN_QFN:QFN-64-1EP_9x9mm_P0.5mm_EP7.15x7.15mm","LTC2290CUP#PBF","Analog Devices","","1"
"U12","ICE40HX4K-TQ144","Package_QFP:TQFP-144_20x20mm_P0.5mm","ICE40HX4K-TQ144","Lattice","","1"
"U13","W25Q32JVSS","Package_SO:SOIC-8_5.3x5.3mm_P1.27mm","W25Q32JVSSIQ","Winbond","","1"
"U14","MT48LC16M16A2TG-6A","Package_SO:TSOP-II-54_22.2x10.16mm_P0.8mm","MT48LC16M16A2P-6A:G","Micron","","1"
"X1","ASE-10.000MHz","Oscillator:Oscillator_SMD_Abracon_ASE-4Pin_3.2x2.5mm","ASE-10.000MHZ-LC-T","Abracon","","1"
"Y1","12MHz","Crystal:Crystal_SMD_3225-4Pin_3.2x2.5mm","ABM8-12.000MHZ-B2-T","Abracon","","1"
